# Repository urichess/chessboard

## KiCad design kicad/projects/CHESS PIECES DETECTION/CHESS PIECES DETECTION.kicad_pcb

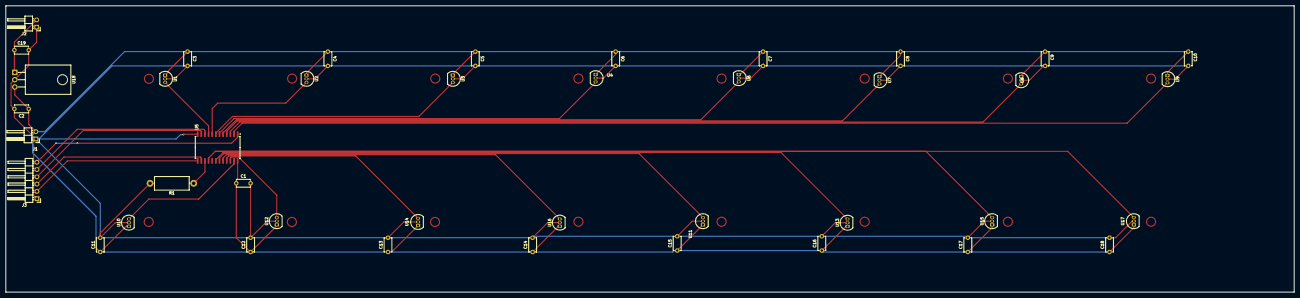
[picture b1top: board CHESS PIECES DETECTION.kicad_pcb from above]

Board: 2 copper layers, 450.0 x 100.0 mm, 41 parts (0 on the bottom side), 24 nets.

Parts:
C1, C2: 0.1uF(10V); C_Disc_D4.7mm_W2.5mm_P5.00mm
C3, C4, C5, C6, C7, C8, C9, C10, C11, C12, C13, C14, C15, C16, C17, C18: 0,1uF; C_Disc_D4.7mm_W2.5mm_P5.00mm
C19: 0.33uF(25V); C_Disc_D4.7mm_W2.5mm_P5.00mm
J1, J2: Conn_01x02; PinHeader_1x02_P2.54mm_Horizontal
J3: Conn_01x06; PinHeader_1x06_P2.54mm_Horizontal
R1: 10K; R_Axial_DIN0414_L11.9mm_D4.5mm_P15.24mm_Horizontal
U1: HALL_SENSOR_1; TO-92_Inline
U2: HALL_SENSOR_2; TO-92_Inline
U3: HALL_SENSOR3; TO-92_Inline
U4: HALL_SENSOR4; TO-92_Inline
U5: CD74HC4067M; SOIC-24W_7.5x15.4mm_P1.27mm
U6: HALL_SENSOR_5; TO-92_Inline
U7: HALL_SENSOR_6; TO-92_Inline
U8: HALL_SENSOR7; TO-92_Inline
U9: HALL_SENSOR8; TO-92_Inline
U10: HALL_SENSOR_9; TO-92_Inline
U11: HALL_SENSOR_13; TO-92_Inline
U12: HALL_SENSOR_10; TO-92_Inline
U13: HALL_SENSOR_14; TO-92_Inline
U14: HALL_SENSOR11; TO-92_Inline
U15: HALL_SENSOR15; TO-92_Inline
U16: HALL_SENSOR12; TO-92_Inline
U17: HALL_SENSOR16; TO-92_Inline
U18: L7805; TO-220-3_Horizontal_TabDown

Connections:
+5V: C1.1, C2.1, C3.1, C4.1, C5.1, C6.1, C7.1, C8.1, C9.1, C10.1, C11.1, C12.1, C13.1, C14.1, C15.1, C16.1, C17.1, C18.1, J1.2, U1.1 (VCC), U2.1 (VCC), U3.1 (VCC), U4.1 (VCC), U5.24 (VCC), U6.1 (VCC), U7.1 (VCC), U8.1 (VCC), U9.1 (VCC), U10.1 (VCC), U11.1 (VCC), U12.1 (VCC), U13.1 (VCC), U14.1 (VCC), U15.1 (VCC), U16.1 (VCC), U17.1 (VCC), U18.3 (OUT)
+6V-12V: C19.1, J2.2, U18.1 (IN)
GND: C1.2, C2.2, C3.2, C4.2, C5.2, C6.2, C7.2, C8.2, C9.2, C10.2, C11.2, C12.2, C13.2, C14.2, C15.2, C16.2, C17.2, C18.2, C19.2, J1.1, J2.1, J3.1, R1.2, U1.2 (GND), U2.2 (GND), U3.2 (GND), U4.2 (GND), U5.12 (GND), U6.2 (GND), U7.2 (GND), U8.2 (GND), U9.2 (GND), U10.2 (GND), U11.2 (GND), U12.2 (GND), U13.2 (GND), U14.2 (GND), U15.2 (GND), U16.2 (GND), U17.2 (GND), U18.2 (GND)
MUX1: J3.5, U5.10 (S0)
MUX2: J3.4, U5.11 (S1)
MUX3: J3.3, U5.14 (S2)
MUX4: J3.2, U5.13 (S3)
unnamed: R1.1, U5.15 (~E)
Output: J3.6, U5.1 (COM)
hall1: U1.3 (OUT), U5.9 (I0)
hall2: U2.3 (OUT), U5.8 (I1)
hall3: U3.3 (OUT), U5.7 (I2)
hall4: U4.3 (OUT), U5.6 (I3)
hall5: U5.5 (I4), U6.3 (OUT)
hall6: U5.4 (I5), U7.3 (OUT)
hall7: U5.3 (I6), U8.3 (OUT)
hall8: U5.2 (I7), U9.3 (OUT)
hall9: U5.23 (I8), U10.3 (OUT)
hall10: U5.22 (I9), U12.3 (OUT)
hall11: U5.21 (I10), U14.3 (OUT)
hall12: U5.20 (I11), U16.3 (OUT)
hall13: U5.19 (I12), U11.3 (OUT)
hall14: U5.18 (I13), U13.3 (OUT)
hall16: U5.16 (I15), U15.3 (OUT), U17.3 (OUT)

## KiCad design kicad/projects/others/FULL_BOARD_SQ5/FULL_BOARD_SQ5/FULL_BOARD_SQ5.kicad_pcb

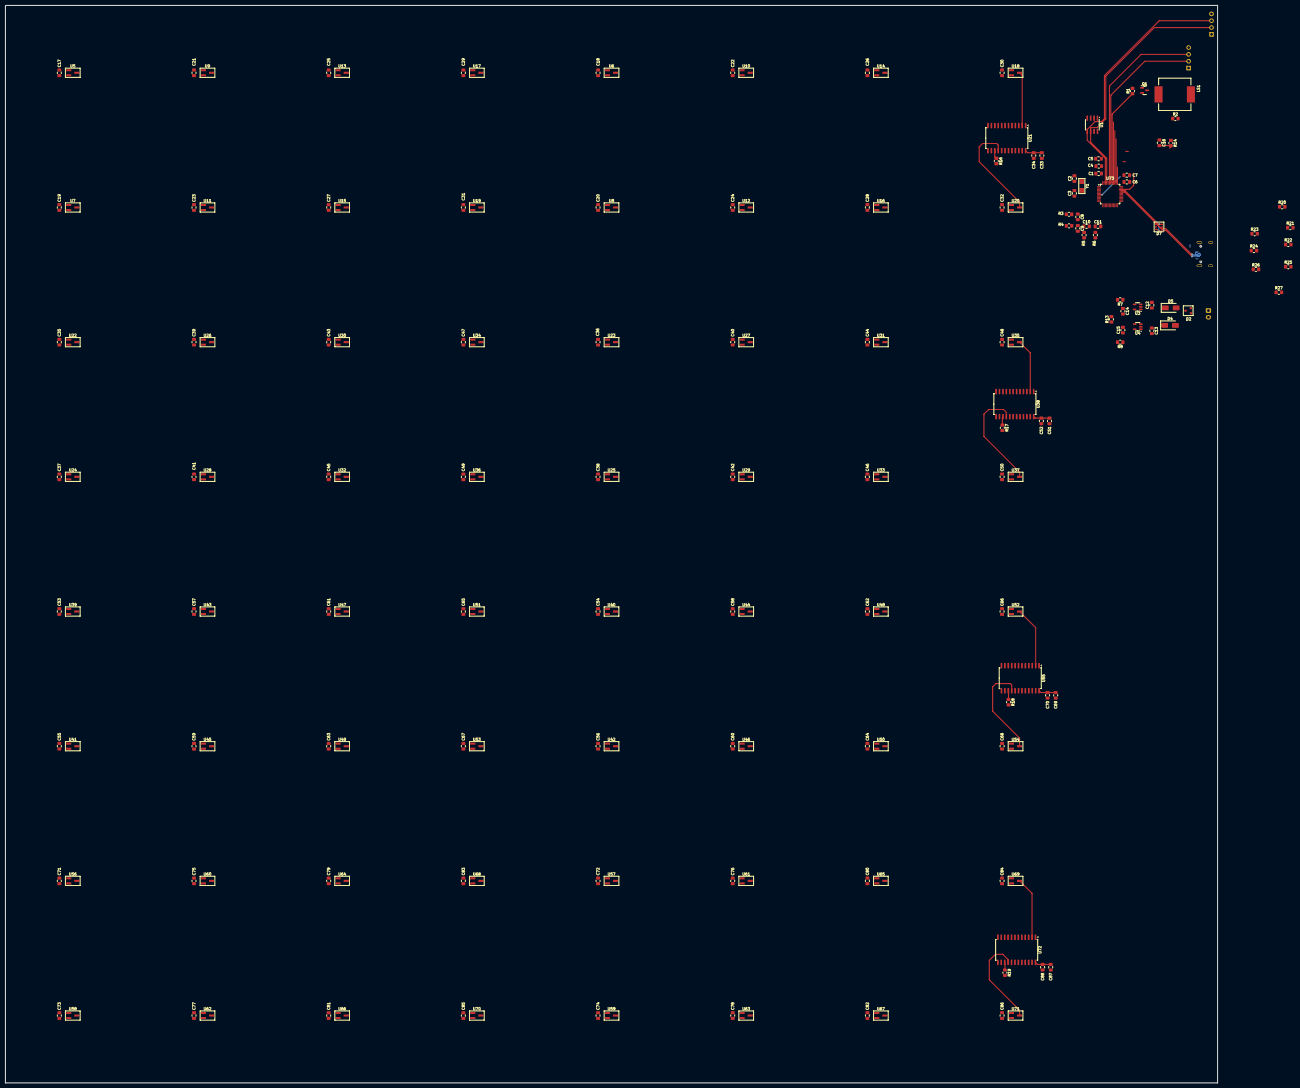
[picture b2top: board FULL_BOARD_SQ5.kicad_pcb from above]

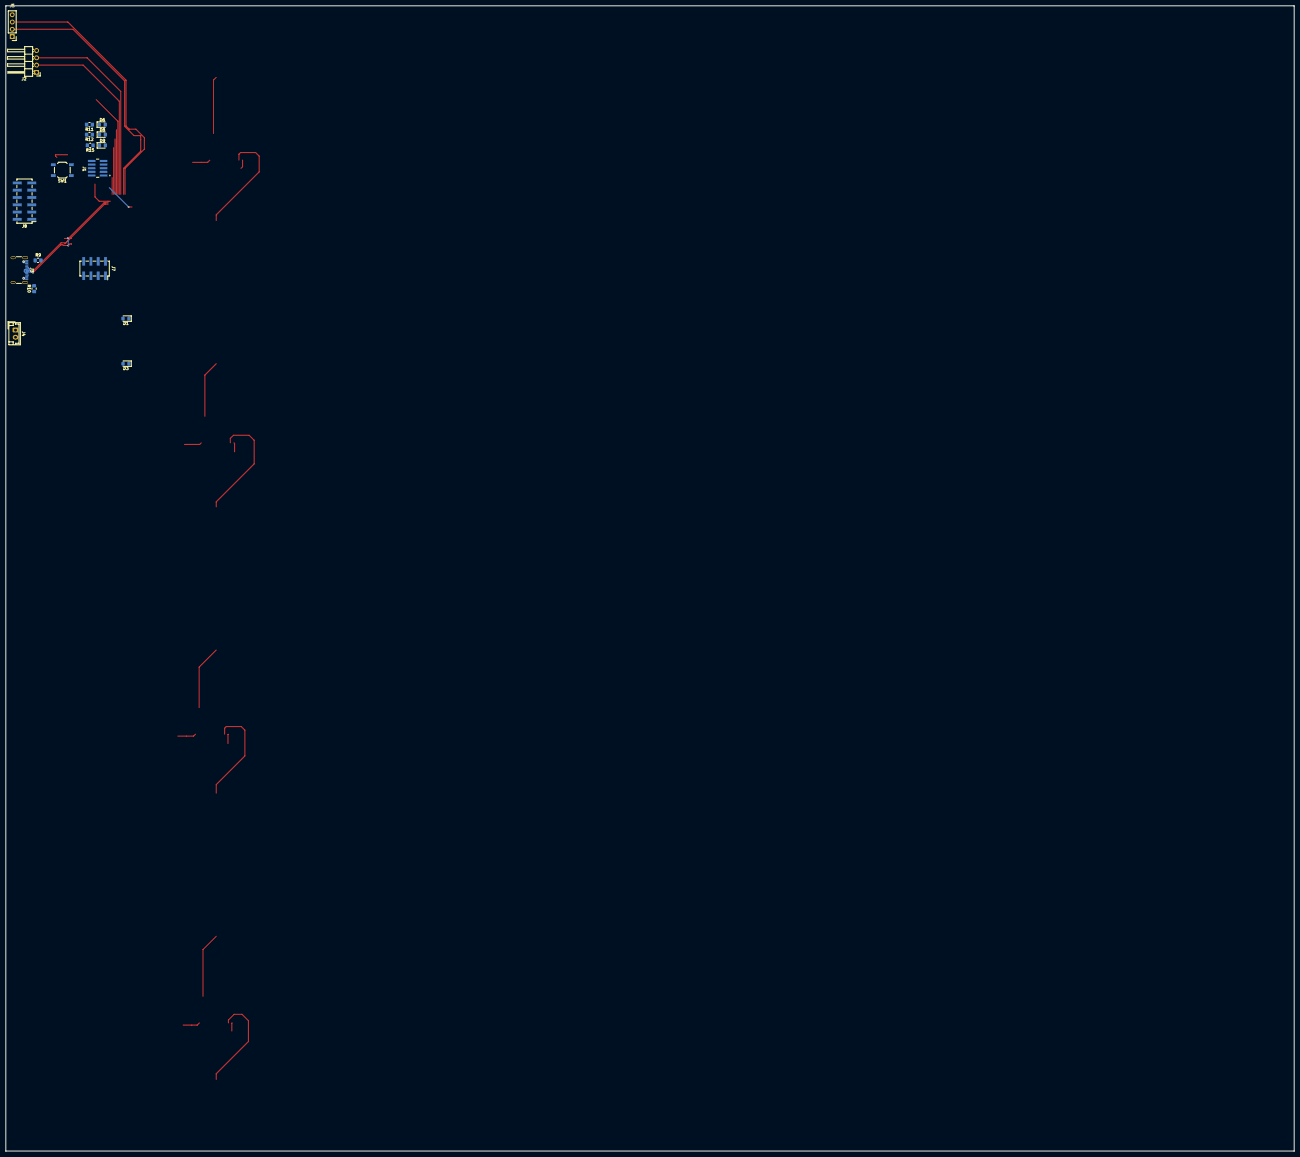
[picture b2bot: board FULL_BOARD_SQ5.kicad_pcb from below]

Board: 2 copper layers, 450.0 x 400.0 mm, 207 parts (18 on the bottom side), 126 nets.

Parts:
C1, C6, C16: 100nF; C_0805_2012Metric_Pad1.18x1.45mm_HandSolder
C2, C3: 3.9pF; C_0805_2012Metric_Pad1.18x1.45mm_HandSolder
C4, C7: 4.7pF; C_0805_2012Metric_Pad1.18x1.45mm_HandSolder
C5, C8, C9, C10, C11, C12, C13, C14, C15, C33, C51, C69, C87: 1uF; C_0805_2012Metric_Pad1.18x1.45mm_HandSolder
C17, C18, C19, C20, C21, C22, C23, C24, C25, C26, C27, C28, C29, C30, C31, C32, C34, C35, C36, C37, C38, C39, C40, C41, C42, C43, C44, C45, C46, C47, C48, C49, C50, C52, C53, C54, C55, C56, C57, C58, C59, C60, C61, C62, C63, C64, C65, C66, C67, C68, C70, C71, C72, C73, C74, C75, C76, C77, C78, C79, C80, C81, C82, C83, C84, C85, C86, C88: 0,1uF; C_0805_2012Metric_Pad1.18x1.45mm_HandSolder
D1, D3, D9: LED_GREEN; LED_0805_2012Metric_Pad1.15x1.40mm_HandSolder
D2: PESD5V0L2BT; SOT-23
D4, D5: SS14; D_SMA
D6: LED_RED; LED_0805_2012Metric_Pad1.15x1.40mm_HandSolder
D7: TVS3V3L4U; TSOP-6_1.65x3.05mm_P0.95mm
D8: LED_ORANGE; LED_0805_2012Metric_Pad1.15x1.40mm_HandSolder
J1: Conn_ARM_JTAG_SWD_10; GCT_BD125-10-A-0305-0580-L-B
J2: UART; PinHeader_1x04_P2.54mm_Horizontal
J3: USB_C_Receptacle_USB2.0_16P; USB_C_Receptacle_GCT_USB4105-xx-A_16P_TopMnt_Horizontal
J4: CONN_2x1; JST_EH_B2B-EH-A_1x02_P2.50mm_Vertical
J5: I2C; PinHeader_1x04_P2.54mm_Vertical
J7: Conn_02x04_Odd_Even; PinSocket_2x04_P2.54mm_Vertical_SMD
J8: Conn_02x06_Odd_Even; PinHeader_2x06_P2.54mm_Vertical_SMD
LS1: CMT-1203-SMT; CUI_CMT-1203-SMT
Q1: BC847; SOT-23
R1: 1k; R_0805_2012Metric_Pad1.20x1.40mm_HandSolder
R2: 47k; R_0805_2012Metric_Pad1.20x1.40mm_HandSolder
R3, R4, R5, R6: 100; R_0805_2012Metric_Pad1.20x1.40mm_HandSolder
R7, R8, R9, R10, R11, R12, R15: 5.1k; R_0805_2012Metric_Pad1.20x1.40mm_HandSolder
R13: 0; R_0805_2012Metric_Pad1.20x1.40mm_HandSolder
R14, R20, R21, R22, R23, R24, R25, R26: 10k; R_0805_2012Metric_Pad1.20x1.40mm_HandSolder
R16, R17, R18, R19: 10K; R_0805_2012Metric_Pad1.20x1.40mm_HandSolder
R27: 100k; R_0805_2012Metric_Pad1.20x1.40mm_HandSolder
SW1: TL3342F450QG; SW_SPST_TL3342
U1: 24LC512; SOIC-8_3.9x4.9mm_P1.27mm
U3, U4: AP2112K-3.3; SOT-23-5
U5, U22, U39, U56: HALL_SENSOR_1; SOT-23_Handsoldering
U6, U23, U40, U57: HALL_SENSOR_5; SOT-23_Handsoldering
U7, U24, U41, U58: HALL_SENSOR_9; SOT-23_Handsoldering
U8, U25, U42, U59: HALL_SENSOR_13; SOT-23_Handsoldering
U9, U26, U43, U60: HALL_SENSOR_2; SOT-23_Handsoldering
U10, U27, U44, U61: HALL_SENSOR_6; SOT-23_Handsoldering
U11, U28, U45, U62: HALL_SENSOR_10; SOT-23_Handsoldering
U12, U29, U46, U63: HALL_SENSOR_14; SOT-23_Handsoldering
U13, U30, U47, U64: HALL_SENSOR3; SOT-23_Handsoldering
U14, U31, U48, U65: HALL_SENSOR7; SOT-23_Handsoldering
U15, U32, U49, U66: HALL_SENSOR11; SOT-23_Handsoldering
U16, U33, U50, U67: HALL_SENSOR15; SOT-23_Handsoldering
U17, U34, U51, U68: HALL_SENSOR4; SOT-23_Handsoldering
U18, U35, U52, U69: HALL_SENSOR8; SOT-23_Handsoldering
U19, U36, U53, U70: HALL_SENSOR12; SOT-23_Handsoldering
U20, U37, U54, U71: HALL_SENSOR16; SOT-23_Handsoldering
U21, U38, U55, U72: CD74HC4067M; SOIC-24W_7.5x15.4mm_P1.27mm
U73: STM32L433CCTx; LQFP-48_7x7mm_P0.5mm
Y1: NX3215SA-32.768KHZ-EXS00A-MU00525; Crystal_SMD_MicroCrystal_CC7V-T1A-2Pin_3.2x1.5mm_HandSolder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

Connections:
3V3_OUT: C15.1, R8.1, R13.1, R26.2, U4.5 (VOUT)
3V3_OUT_EN: U4.3 (EN), U73.25 (PB12)
5V_IN: C12.1, C13.1, D4.1 (K), D5.1 (K), U3.1 (VIN), U3.3 (EN), U4.1 (VIN)
5V_USB: D2.2 (A2), D5.2 (A), J3.A4 (VBUS), J3.A9 (VBUS), J3.B4 (VBUS), J3.B9 (VBUS)
+3V3: C1.1, C4.1, C5.1, C6.1, C7.1, C14.1, C17.1, C18.1, C19.1, C20.1, C21.1, C22.1, C23.1, C24.1, C25.1, C26.1, C27.1, C28.1, C29.1, C30.1, C31.1, C32.1, C33.1, C34.1, C35.1, C36.1, C37.1, C38.1, C39.1, C40.1, C41.1, C42.1, C43.1, C44.1, C45.1, C46.1, C47.1, C48.1, C49.1, C50.1, C51.1, C52.1, C53.1, C54.1, C55.1, C56.1, C57.1, C58.1, C59.1, C60.1, C61.1, C62.1, C63.1, C64.1, C65.1, C66.1, C67.1, C68.1, C69.1, C70.1, C71.1, C72.1, C73.1, C74.1, C75.1, C76.1, C77.1, C78.1, C79.1, C80.1, C81.1, C82.1, C83.1, C84.1, C85.1, C86.1, C87.1, C88.1, J1.1 (VTref), J2.4, J5.4, J7.2, J8.1, J8.2, LS1.1, R2.2, R7.1, R13.2, R14.1, R20.1, R22.1, R24.1, U1.8 (VCC), U3.5 (VOUT), U5.1 (VCC), U6.1 (VCC), U7.1 (VCC), U8.1 (VCC), U9.1 (VCC), U10.1 (VCC), U11.1 (VCC), U12.1 (VCC), U13.1 (VCC), U14.1 (VCC), U15.1 (VCC), U16.1 (VCC), U17.1 (VCC), U18.1 (VCC), U19.1 (VCC), U20.1 (VCC), U21.24 (VCC), U22.1 (VCC), U23.1 (VCC), U24.1 (VCC), U25.1 (VCC), U26.1 (VCC), U27.1 (VCC), U28.1 (VCC), U29.1 (VCC), U30.1 (VCC), U31.1 (VCC), U32.1 (VCC), U33.1 (VCC), U34.1 (VCC), U35.1 (VCC), U36.1 (VCC), U37.1 (VCC), U38.24 (VCC), U39.1 (VCC), U40.1 (VCC), U41.1 (VCC), U42.1 (VCC), U43.1 (VCC), U44.1 (VCC), U45.1 (VCC), U46.1 (VCC), U47.1 (VCC), U48.1 (VCC), U49.1 (VCC), U50.1 (VCC), U51.1 (VCC), U52.1 (VCC), U53.1 (VCC), U54.1 (VCC), U55.24 (VCC), U56.1 (VCC), U57.1 (VCC), U58.1 (VCC), U59.1 (VCC), U60.1 (VCC), U61.1 (VCC), U62.1 (VCC), U63.1 (VCC), U64.1 (VCC), U65.1 (VCC), U66.1 (VCC), U67.1 (VCC), U68.1 (VCC), U69.1 (VCC), U70.1 (VCC), U71.1 (VCC), U72.24 (VCC), U73.1 (VBAT), U73.9 (VDDA), U73.24 (VDD), U73.36 (VDDUSB), U73.48 (VDD)
/sensor_matrix0/hall1: U5.3 (OUT), U21.9 (I0)
/sensor_matrix0/hall2: U9.3 (OUT), U21.8 (I1)
/sensor_matrix0/hall3: U13.3 (OUT), U21.7 (I2)
/sensor_matrix0/hall4: U17.3 (OUT), U21.6 (I3)
/sensor_matrix0/hall5: U6.3 (OUT), U21.5 (I4)
/sensor_matrix0/hall6: U10.3 (OUT), U21.4 (I5)
/sensor_matrix0/hall7: U14.3 (OUT), U21.3 (I6)
/sensor_matrix0/hall8: U18.3 (OUT), U21.2 (I7)
/sensor_matrix0/hall9: U7.3 (OUT), U21.23 (I8)
/sensor_matrix0/hall10: U11.3 (OUT), U21.22 (I9)
/sensor_matrix0/hall11: U15.3 (OUT), U21.21 (I10)
/sensor_matrix0/hall12: U19.3 (OUT), U21.20 (I11)
/sensor_matrix0/hall13: U8.3 (OUT), U21.19 (I12)
/sensor_matrix0/hall14: U12.3 (OUT), U21.18 (I13)
/sensor_matrix0/hall15: U16.3 (OUT), U21.17 (I14)
/sensor_matrix0/hall16: U20.3 (OUT), U21.16 (I15)
/sensor_matrix1/hall1: U22.3 (OUT), U38.9 (I0)
/sensor_matrix1/hall2: U26.3 (OUT), U38.8 (I1)
/sensor_matrix1/hall3: U30.3 (OUT), U38.7 (I2)
/sensor_matrix1/hall4: U34.3 (OUT), U38.6 (I3)
/sensor_matrix1/hall5: U23.3 (OUT), U38.5 (I4)
/sensor_matrix1/hall6: U27.3 (OUT), U38.4 (I5)
/sensor_matrix1/hall7: U31.3 (OUT), U38.3 (I6)
/sensor_matrix1/hall8: U35.3 (OUT), U38.2 (I7)
/sensor_matrix1/hall9: U24.3 (OUT), U38.23 (I8)
/sensor_matrix1/hall10: U28.3 (OUT), U38.22 (I9)
/sensor_matrix1/hall11: U32.3 (OUT), U38.21 (I10)
/sensor_matrix1/hall12: U36.3 (OUT), U38.20 (I11)
/sensor_matrix1/hall13: U25.3 (OUT), U38.19 (I12)
/sensor_matrix1/hall14: U29.3 (OUT), U38.18 (I13)
/sensor_matrix1/hall15: U33.3 (OUT), U38.17 (I14)
/sensor_matrix1/hall16: U37.3 (OUT), U38.16 (I15)
/sensor_matrix2/hall1: U39.3 (OUT), U55.9 (I0)
/sensor_matrix2/hall2: U43.3 (OUT), U55.8 (I1)
/sensor_matrix2/hall3: U47.3 (OUT), U55.7 (I2)
/sensor_matrix2/hall4: U51.3 (OUT), U55.6 (I3)
/sensor_matrix2/hall5: U40.3 (OUT), U55.5 (I4)
/sensor_matrix2/hall6: U44.3 (OUT), U55.4 (I5)
/sensor_matrix2/hall7: U48.3 (OUT), U55.3 (I6)
/sensor_matrix2/hall8: U52.3 (OUT), U55.2 (I7)
/sensor_matrix2/hall9: U41.3 (OUT), U55.23 (I8)
/sensor_matrix2/hall10: U45.3 (OUT), U55.22 (I9)
/sensor_matrix2/hall11: U49.3 (OUT), U55.21 (I10)
/sensor_matrix2/hall12: U53.3 (OUT), U55.20 (I11)
/sensor_matrix2/hall13: U42.3 (OUT), U55.19 (I12)
/sensor_matrix2/hall14: U46.3 (OUT), U55.18 (I13)
/sensor_matrix2/hall15: U50.3 (OUT), U55.17 (I14)
/sensor_matrix2/hall16: U54.3 (OUT), U55.16 (I15)
/sensor_matrix3/hall1: U56.3 (OUT), U72.9 (I0)
/sensor_matrix3/hall2: U60.3 (OUT), U72.8 (I1)
/sensor_matrix3/hall3: U64.3 (OUT), U72.7 (I2)
/sensor_matrix3/hall4: U68.3 (OUT), U72.6 (I3)
/sensor_matrix3/hall5: U57.3 (OUT), U72.5 (I4)
/sensor_matrix3/hall6: U61.3 (OUT), U72.4 (I5)
/sensor_matrix3/hall7: U65.3 (OUT), U72.3 (I6)
/sensor_matrix3/hall8: U69.3 (OUT), U72.2 (I7)
/sensor_matrix3/hall9: U58.3 (OUT), U72.23 (I8)
/sensor_matrix3/hall10: U62.3 (OUT), U72.22 (I9)
/sensor_matrix3/hall11: U66.3 (OUT), U72.21 (I10)
/sensor_matrix3/hall12: U70.3 (OUT), U72.20 (I11)
/sensor_matrix3/hall13: U59.3 (OUT), U72.19 (I12)
/sensor_matrix3/hall14: U63.3 (OUT), U72.18 (I13)
/sensor_matrix3/hall15: U67.3 (OUT), U72.17 (I14)
/sensor_matrix3/hall16: U71.3 (OUT), U72.16 (I15)
BUZZER_PWM: R1.1, U73.41 (PB5)
EXPANSION0: J8.3, U73.21 (PB10)
EXPANSION1: J8.5, U73.22 (PB11)
EXPANSION2: J8.7, U73.26 (PB13)
EXPANSION3: J8.9, U73.27 (PB14)
EXPANSION4: J8.11, U73.28 (PB15)
FBK_3V3_SENSORS: R26.1, R27.1, U73.19 (PB1)
GND: C1.2, C2.2, C3.2, C4.2, C5.2, C6.2, C7.2, C8.2, C9.2, C10.2, C11.2, C12.2, C13.2, C14.2, C15.2, C16.1, C17.2, C18.2, C19.2, C20.2, C21.2, C22.2, C23.2, C24.2, C25.2, C26.2, C27.2, C28.2, C29.2, C30.2, C31.2, C32.2, C33.2, C34.2, C35.2, C36.2, C37.2, C38.2, C39.2, C40.2, C41.2, C42.2, C43.2, C44.2, C45.2, C46.2, C47.2, C48.2, C49.2, C50.2, C51.2, C52.2, C53.2, C54.2, C55.2, C56.2, C57.2, C58.2, C59.2, C60.2, C61.2, C62.2, C63.2, C64.2, C65.2, C66.2, C67.2, C68.2, C69.2, C70.2, C71.2, C72.2, C73.2, C74.2, C75.2, C76.2, C77.2, C78.2, C79.2, C80.2, C81.2, C82.2, C83.2, C84.2, C85.2, C86.2, C87.2, C88.2, D1.1 (K), D2.3 (Com), D3.1 (K), J1.3 (GND), J1.5 (GND), J1.9 (GNDDetect), J2.1, J3.A1 (GND), J3.A12 (GND), J3.B1 (GND), J3.B12 (GND), J3.S1 (SHIELD), J4.1, J5.1, J7.1, J8.4, J8.6, J8.8, J8.10, J8.12, Q1.2 (E), R9.2, R10.2, R11.2, R12.2, R15.2, R16.2, R17.2, R18.2, R19.2, R21.2, R23.2, R25.2, R27.2, SW1.1, U1.1 (A0), U1.2 (A1), U1.3 (A2), U1.4 (GND), U1.7 (WP), U3.2 (GND), U4.2 (GND), U5.2 (GND), U6.2 (GND), U7.2 (GND), U8.2 (GND), U9.2 (GND), U10.2 (GND), U11.2 (GND), U12.2 (GND), U13.2 (GND), U14.2 (GND), U15.2 (GND), U16.2 (GND), U17.2 (GND), U18.2 (GND), U19.2 (GND), U20.2 (GND), U21.12 (GND), U22.2 (GND), U23.2 (GND), U24.2 (GND), U25.2 (GND), U26.2 (GND), U27.2 (GND), U28.2 (GND), U29.2 (GND), U30.2 (GND), U31.2 (GND), U32.2 (GND), U33.2 (GND), U34.2 (GND), U35.2 (GND), U36.2 (GND), U37.2 (GND), U38.12 (GND), U39.2 (GND), U40.2 (GND), U41.2 (GND), U42.2 (GND), U43.2 (GND), U44.2 (GND), U45.2 (GND), U46.2 (GND), U47.2 (GND), U48.2 (GND), U49.2 (GND), U50.2 (GND), U51.2 (GND), U52.2 (GND), U53.2 (GND), U54.2 (GND), U55.12 (GND), U56.2 (GND), U57.2 (GND), U58.2 (GND), U59.2 (GND), U60.2 (GND), U61.2 (GND), U62.2 (GND), U63.2 (GND), U64.2 (GND), U65.2 (GND), U66.2 (GND), U67.2 (GND), U68.2 (GND), U69.2 (GND), U70.2 (GND), U71.2 (GND), U72.12 (GND), U73.8 (VSSA), U73.23 (VSS), U73.35 (VSS), U73.47 (VSS)
HWREV0: R22.2, R23.1, U73.29 (PA8)
HWREV2: R24.2, R25.1
I2C_CLK: J5.2, U1.6 (SCL), U73.45 (PB8)
I2C_DATA: J5.3, U1.5 (SDA), U73.46 (PB9)
LED_ALIVE: D6.2 (A), U73.40 (PB4)
LED_USER1: D8.2 (A), U73.39 (PB3)
LED_USER2: D9.2 (A), U73.38 (PA15)
MUX1: U21.10 (S0), U38.10 (S0), U55.10 (S0), U72.10 (S0), U73.10 (PA0)
MUX2: U21.11 (S1), U38.11 (S1), U55.11 (S1), U72.11 (S1), U73.6 (PH1)
MUX3: U21.14 (S2), U38.14 (S2), U55.14 (S2), U72.14 (S2), U73.5 (PH0)
MUX4: U21.13 (S3), U38.13 (S3), U55.13 (S3), U72.13 (S3), U73.2 (PC13)
NRF24_CE: J7.3, U73.31 (PA10)
NRF24_CSN: J7.4, U73.18 (PB0)
NRF24_IRQ: J7.8, U73.20 (PB2)
NRF24_MISO: J7.7, U73.16 (PA6)
NRF24_MOSI: J7.6, U73.17 (PA7)
NRF24_SCK: J7.5, U73.15 (PA5)
NRST: C16.2, J1.10 (~RESET), R14.2, SW1.2, U73.7 (NRST)
unnamed: D1.2 (A), R7.2
unnamed: D2.1 (A1), D4.2 (A), J4.2
unnamed: D3.2 (A), R8.2
unnamed: D6.1 (K), R11.1
unnamed: D8.1 (K), R12.1
unnamed: D9.1 (K), R15.1
unnamed: J3.A5 (CC1), R9.1
unnamed: J3.B5 (CC2), R10.1
unnamed: Q1.1 (B), R1.2
unnamed: LS1.2, Q1.3 (C), R2.1
unnamed: R20.2, R21.1
unnamed: R16.1, U21.15 (~E)
unnamed: R17.1, U38.15 (~E)
unnamed: R18.1, U55.15 (~E)
unnamed: R19.1, U72.15 (~E)
unnamed: C8.1, R3.2, U73.11 (PA1)
unnamed: C9.1, R4.2, U73.12 (PA2)
unnamed: C10.1, R5.2, U73.13 (PA3)
unnamed: C11.1, R6.2, U73.14 (PA4)
unnamed: C2.1, U73.3 (PC14), Y1.1
unnamed: C3.1, U73.4 (PC15), Y1.2
SIG1: R3.1, U21.1 (COM)
SIG2: R4.1, U38.1 (COM)
SIG3: R5.1, U55.1 (COM)
SIG4: R6.1, U72.1 (COM)
SWCLK: J1.4 (SWCLK/TCK), U73.37 (PA14)
SWDIO: J1.2 (SWDIO/TMS), U73.34 (PA13)
UART_OUT_RX: J2.3, U73.43 (PB7)
UART_OUT_TX: J2.2, U73.42 (PB6)
USB_N: D7.1 (L1), D7.4 (L3), J3.A7 (D-), J3.B7 (D-), U73.32 (PA11)
USB_P: D7.3 (L2), D7.6 (L4), J3.A6 (D+), J3.B6 (D+), U73.33 (PA12)
